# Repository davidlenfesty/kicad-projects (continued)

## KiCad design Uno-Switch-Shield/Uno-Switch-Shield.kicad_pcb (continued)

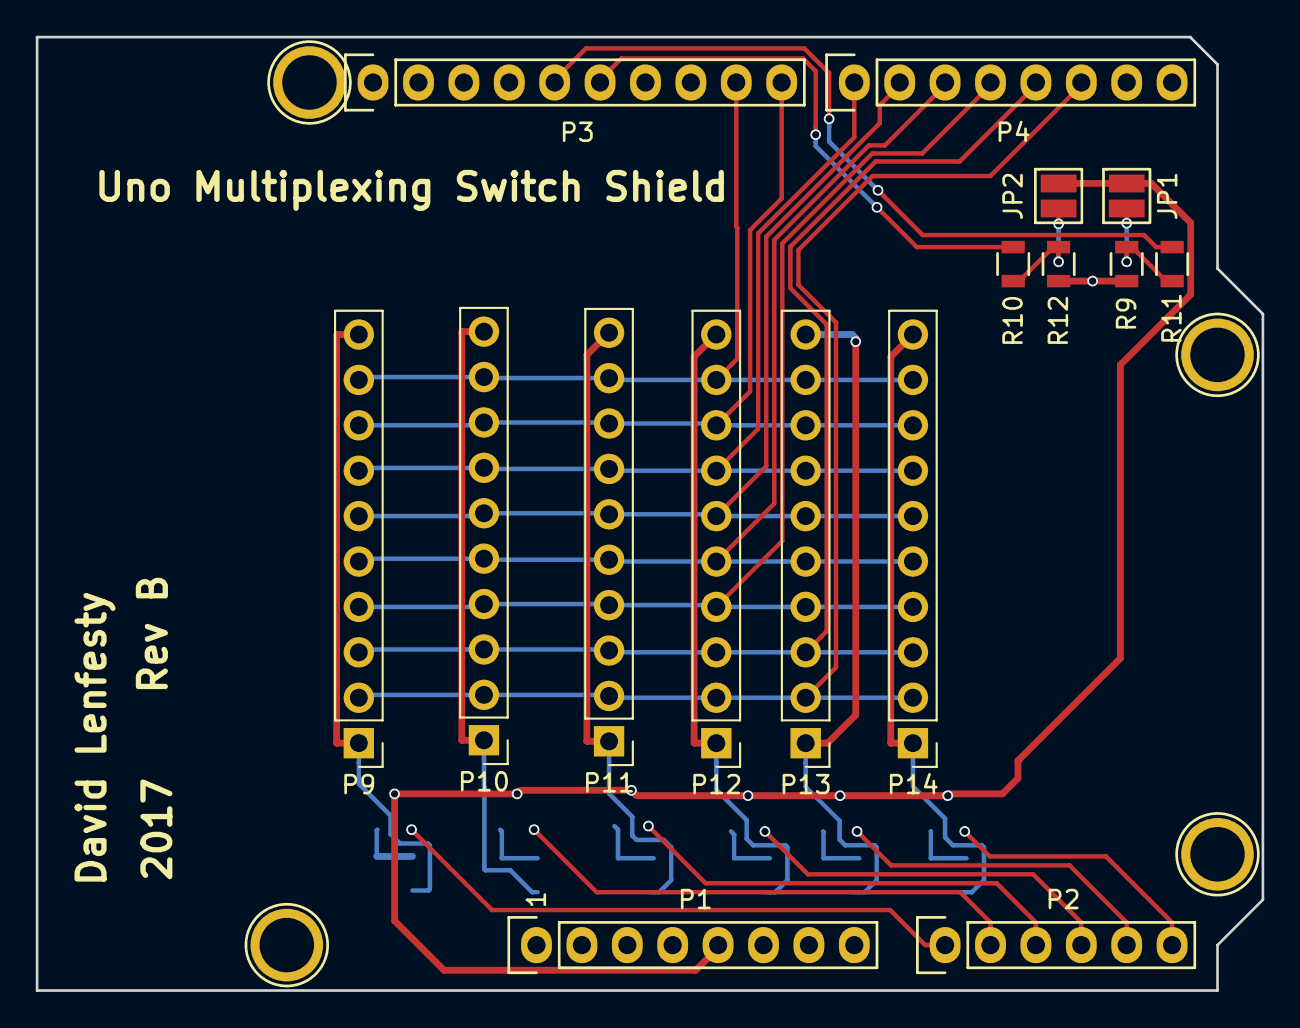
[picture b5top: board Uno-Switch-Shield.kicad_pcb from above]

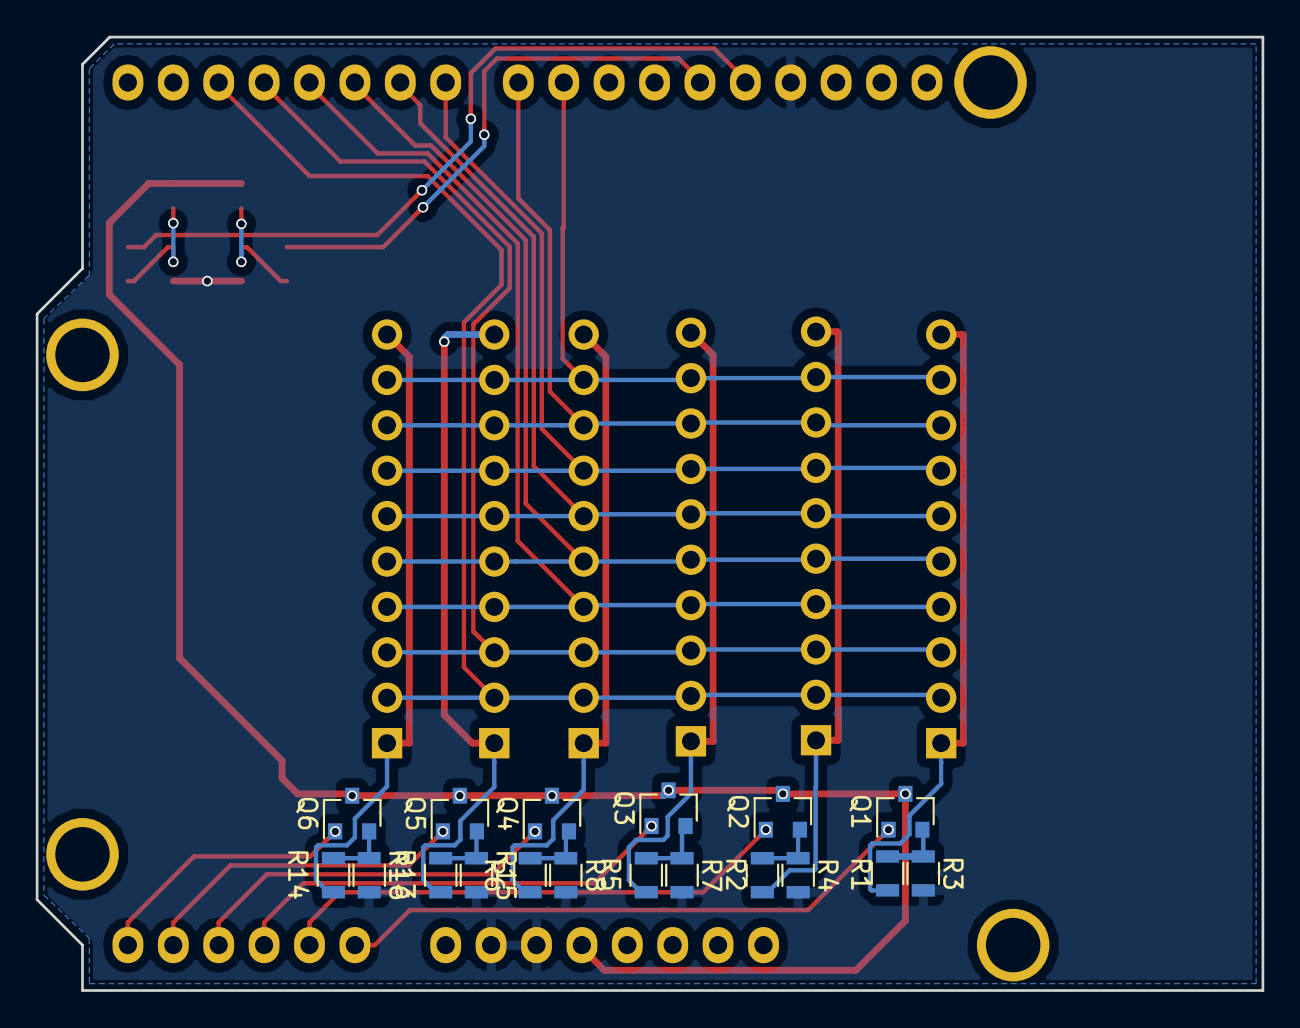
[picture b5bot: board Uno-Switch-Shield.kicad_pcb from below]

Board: 2 copper layers, 68.6 x 53.3 mm, 38 parts (18 on the bottom side), 32 nets.

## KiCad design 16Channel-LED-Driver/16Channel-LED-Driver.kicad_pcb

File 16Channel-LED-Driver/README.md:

# 16 Channel LED Driver Board #

## Intro ##

This is a 16 Channel LED Driver board. Each channel has current limiting (set by the potentiometre/resistor combo by each opamp) and is PWM dimmable. It uses two PCA9634s to do the dimming. Sometime soon I'll come up with a full BOM.

## Decisions ##

I used two PCA9634s and four LM324s just to simplify the routing because initially I figured a two layer board would be simpler to design for personally.

## Revisions ##

### Revision A ###

This was the first revision of the board, had a bunch of issues to fix, a lot of them dumb.

### Revision B ###

The main issue with this revision was lack of resistors in front of the BJTs, so it would pull too much current and overheat the PCA9634s.

### Revision C ###

An issue with the opamp stuff, if you had too high a value for the potentiometre, it would overdrive the BJTs and wreck the opamp.

### Revision D ###

Probably the last revision, unless I decide to completely redo it to make it nicer or put it on a 4 layer board to reduce the size.

## Errata ##

- Consider Rev A and Rev B unusable versions of this board.
- Rev C has an issue where if you turn the potentiometre all the way it will fry the opamp, trying to fix that with Rev D, which as of this commit is not started.

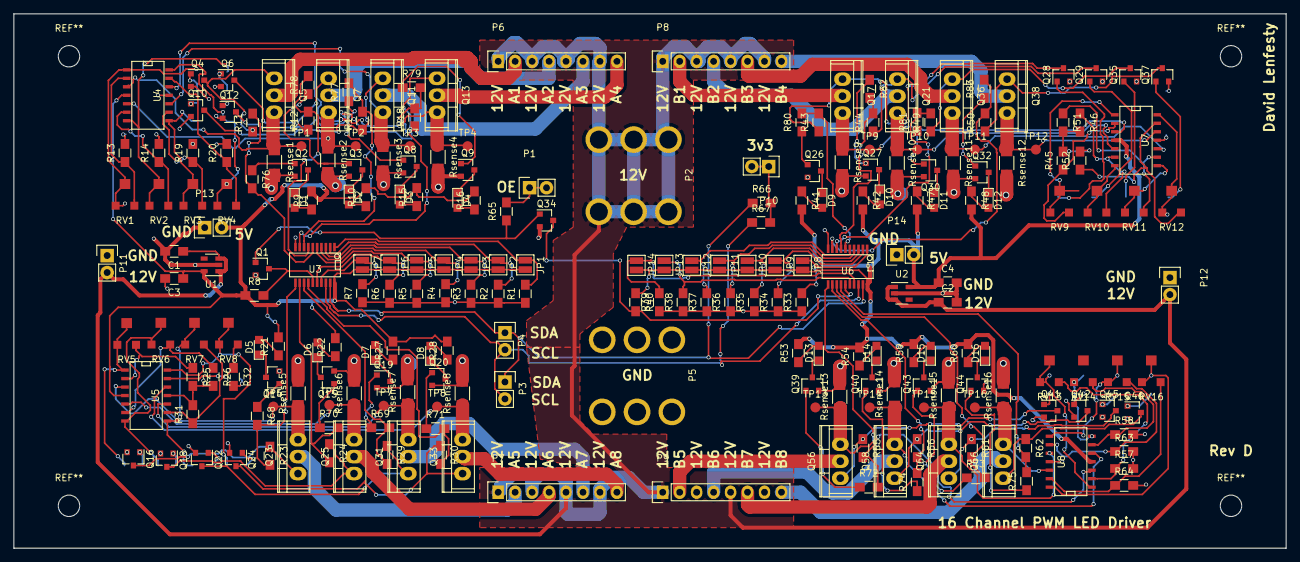
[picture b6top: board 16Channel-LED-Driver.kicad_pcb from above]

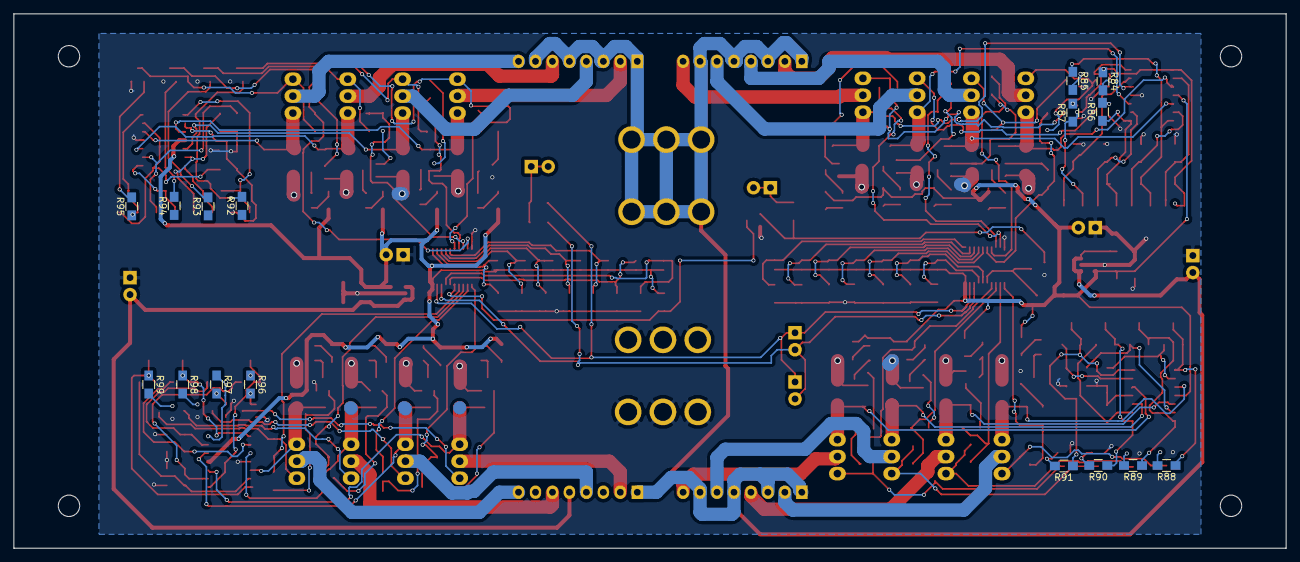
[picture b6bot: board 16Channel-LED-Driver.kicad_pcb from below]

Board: 2 copper layers, 190.5 x 80.0 mm, 253 parts (16 on the bottom side), 185 nets.

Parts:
C1, C2, C3, C4: 1uF; R_0805_HandSoldering
D1, D2, D3, D4, D5, D6, D7, D8, D9, D10, D11, D12, D13, D14, D15, D16: LED; LED_0805
JP1, JP8: A0; Jumper_SMD
JP2, JP9: A1; Jumper_SMD
JP3, JP10: A2; Jumper_SMD
JP4, JP11: A3; Jumper_SMD
JP5, JP12: A4; Jumper_SMD
JP6, JP13: A5; Jumper_SMD
JP7, JP14: A6; Jumper_SMD
P1, P3, P4, P10, P11, P12, P13, P14: CONN_01X02; Socket_Strip_Straight_1x02
P2, P5: CONN_01X06; Screw_Connector_M5
P6, P7, P8, P9: CONN_01X08; Socket_Strip_Straight_1x08
Q1, Q2, Q3, Q4, Q6, Q8, Q9, Q10, Q12, Q14, Q15, Q16, Q18, Q19, Q20, Q22, Q24, Q26, Q27, Q28, Q29, Q30, Q32, Q34, Q35, Q37, Q39, Q40, Q41, Q42, Q43, Q44, Q45, Q46: Q_NPN_BEC; SOT-23
Q5, Q7, Q11, Q13, Q17, Q21, Q23, Q25, Q31, Q33, Q36, Q38, Q56, Q58, Q64, Q66: BUT11; TO-220
R1, R2, R3, R4, R5, R6, R7, R8, R11, R12, R17, R18, R23, R24, R29, R30, R33, R34, R35, R36, R37, R38, R39, R40, R43, R44, R49, R50, R55, R56, R61, R62, R65, R68, R69, R70, R71, R72, R73, R74, R75, R76, R77, R78, R79, R80, R81, R82, R83, R84, R85, R86, R87, R88, R89, R90, R91, R92, R93, R94, R95, R96, R97, R98, R99: 10K; R_0805_HandSoldering
R9, R10, R15, R16, R21, R22, R27, R28, R41, R42, R47, R48, R53, R54, R59, R60: 330; R_0805_HandSoldering
R13, R14, R19, R20, R25, R26, R31, R32, R45, R46, R51, R52, R57, R58, R63, R64: 2K; R_0805_HandSoldering
R66, R67: 4.7K; R_0805_HandSoldering
RV1, RV2, RV3, RV4, RV5, RV6, RV7, RV8, RV9, RV10, RV11, RV12, RV13, RV14, RV15, RV16: 10K; Bourns-TC33
Rsense1, Rsense2, Rsense3, Rsense4, Rsense5, Rsense6, Rsense7, Rsense8, Rsense9, Rsense10, Rsense11, Rsense12, Rsense13, Rsense14, Rsense15, Rsense16: 0.1; R_1206_HandSoldering
TP1, TP2, TP3, TP4, TP5, TP6, TP7, TP8, TP9, TP10, TP11, TP12, TP13, TP14, TP15, TP16: TEST; Measurement_Point_Round-SMD-Pad_Small
U1, U2: LD3985G; SOT-23-5
U3, U6: PCA9634; SSOP-20
U4, U5, U7, U8: LM324AN; SOIC-14_N

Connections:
+3V3: P10.1, P10.2, R66.2, R67.2
+5V-A: C3.1, JP1.2, JP2.2, JP3.2, JP4.2, JP5.2, JP6.2, JP7.2, P13.2, R8.1, R9.2, R10.2, R15.2, R16.2, R21.2, R22.2, R27.2, R28.2, U1.5, U3.20, U4.4, U5.4
+5V-B: C4.1, JP8.2, JP9.2, JP10.2, JP11.2, JP12.2, JP13.2, JP14.2, P14.2, R40.1, R41.2, R42.2, R47.2, R48.2, R53.2, R54.2, R59.2, R60.2, U2.5, U6.20, U7.4, U8.4
+12V: C1.1, C2.1, P2.1, P2.2, P2.3, P2.4, P2.5, P2.6, P6.1, P6.3, P6.5, P6.7, P7.1, P7.3, P7.5, P7.7, P8.1, P8.3, P8.5, P8.7, P9.1, P9.3, P9.5, P9.7, P11.2, P12.2, U1.1, U1.3, U2.1, U2.3
/Power Driver A/LED Driver A/LED1: R11.2, R76.2, U3.6
/Power Driver A/LED Driver A/LED2: R12.2, R78.2, U3.7
/Power Driver A/LED Driver A/LED3: R17.2, R77.2, U3.8
/Power Driver A/LED Driver A/LED4: R18.2, R79.2, U3.9
/Power Driver A/LED Driver B/LED1: R23.2, R68.2, U3.11
/Power Driver A/LED Driver B/LED2: R24.2, R70.2, U3.12
/Power Driver A/LED Driver B/LED3: R29.2, R69.2, U3.13
/Power Driver A/LED Driver B/LED4: R30.2, R71.2, U3.14
/Power Driver B/LED Driver A/LED1: R43.2, R80.2, U6.6
/Power Driver B/LED Driver A/LED2: R44.2, R82.2, U6.7
/Power Driver B/LED Driver A/LED3: R49.2, R81.2, U6.8
/Power Driver B/LED Driver A/LED4: R50.2, R83.2, U6.9
/Power Driver B/LED Driver B/LED1: R55.2, R72.2, U6.11
/Power Driver B/LED Driver B/LED2: R56.2, R74.2, U6.12
/Power Driver B/LED Driver B/LED3: R61.2, R73.2, U6.13
/Power Driver B/LED Driver B/LED4: R62.2, R75.2, U6.14
GND: C1.2, C2.2, C3.2, C4.2, P5.1, P5.2, P5.3, P5.4, P5.5, P5.6, P11.1, P12.1, P13.1, P14.1, Q1.2, Q2.2, Q3.2, Q4.2, Q6.2, Q8.2, Q9.2, Q10.2, Q12.2, Q14.2, Q15.2, Q16.2, Q18.2, Q19.2, Q20.2, Q22.2, Q24.2, Q26.2, Q27.2, Q28.2, Q29.2, Q30.2, Q32.2, Q34.2, Q35.2, Q37.2, Q39.2, Q40.2, Q41.2, Q42.2, Q43.2, Q44.2, Q45.2, Q46.2, R1.1, R2.1, R3.1, R4.1, R5.1, R6.1, R7.1, R13.2, R14.2, R19.2, R20.2, R25.2, R26.2, R31.2, R32.2, R33.1, R34.1, R35.1, R36.1, R37.1, R38.1, R39.1, R45.2, R46.2, R51.2, R52.2, R57.2, R58.2, R63.2, R64.2, Rsense1.2, Rsense2.2, Rsense3.2, Rsense4.2, Rsense5.2, Rsense6.2, Rsense7.2, Rsense8.2, Rsense9.2, Rsense10.2, Rsense11.2, Rsense12.2, Rsense13.2, Rsense14.2, Rsense15.2, Rsense16.2, U1.2, U2.2, U3.10, U4.11, U5.11, U6.10, U7.11, U8.11
unnamed: D1.1, Q2.3
unnamed: D1.2, R9.1
unnamed: D2.1, Q3.3
unnamed: D2.2, R10.1
unnamed: D3.1, Q8.3
unnamed: D3.2, R15.1
unnamed: D4.1, Q9.3
unnamed: D4.2, R16.1
unnamed: D5.1, Q14.3
unnamed: D5.2, R21.1
unnamed: D6.1, Q15.3
unnamed: D6.2, R22.1
unnamed: D7.1, Q19.3
unnamed: D7.2, R27.1
unnamed: D8.1, Q20.3
unnamed: D8.2, R28.1
unnamed: D9.1, Q26.3
unnamed: D9.2, R41.1
unnamed: D10.1, Q27.3
unnamed: D10.2, R42.1
unnamed: D11.1, Q30.3
unnamed: D11.2, R47.1
unnamed: D12.1, Q32.3
unnamed: D12.2, R48.1
unnamed: D13.1, Q39.3
unnamed: D13.2, R53.1
unnamed: D14.1, Q40.3
unnamed: D14.2, R54.1
unnamed: D15.1, Q43.3
unnamed: D15.2, R59.1
unnamed: D16.1, Q44.3
unnamed: D16.2, R60.1
unnamed: JP1.1, R1.2, U3.1
unnamed: JP2.1, R2.2, U3.2
unnamed: JP3.1, R3.2, U3.3
unnamed: JP4.1, R4.2, U3.4
unnamed: JP5.1, R5.2, U3.5
unnamed: JP6.1, R6.2, U3.16
unnamed: JP7.1, R7.2, U3.17
unnamed: JP8.1, R33.2, U6.1
unnamed: JP9.1, R34.2, U6.2
unnamed: JP10.1, R35.2, U6.3
unnamed: JP11.1, R36.2, U6.4
unnamed: JP12.1, R37.2, U6.5
unnamed: JP13.1, R38.2, U6.16
unnamed: JP14.1, R39.2, U6.17
unnamed: P1.1, P1.2, R65.2
unnamed: P6.2, Q5.2
unnamed: P6.4, Q7.2
unnamed: P6.6, Q11.2
unnamed: P6.8, Q13.2
unnamed: P7.2, Q23.2
unnamed: P7.4, Q25.2
unnamed: P7.6, Q31.2
unnamed: P7.8, Q33.2
unnamed: P8.2, Q17.2
unnamed: P8.4, Q21.2
unnamed: P8.6, Q36.2
unnamed: P8.8, Q38.2
unnamed: P9.2, Q56.2
unnamed: P9.4, Q58.2
unnamed: P9.6, Q64.2
unnamed: P9.8, Q66.2
unnamed: Q1.3, R8.2, U3.15
unnamed: Q2.1, R76.1
unnamed: Q3.1, R78.1
unnamed: Q4.1, R84.2
unnamed: Q4.3, Q5.1, R11.1
unnamed: Q5.3, Rsense1.1, TP1.1, U4.3
unnamed: Q6.1, R85.2
unnamed: Q6.3, Q7.1, R12.1
unnamed: Q7.3, Rsense2.1, TP2.1, U4.5
unnamed: Q8.1, R77.1
unnamed: Q9.1, R79.1
unnamed: Q10.1, R86.2
unnamed: Q10.3, Q11.1, R17.1
unnamed: Q11.3, Rsense3.1, TP3.1, U4.10
unnamed: Q12.1, R87.2
unnamed: Q12.3, Q13.1, R18.1
unnamed: Q13.3, Rsense4.1, TP4.1, U4.12
unnamed: Q14.1, R68.1
unnamed: Q15.1, R70.1
unnamed: Q16.1, R88.2
unnamed: Q16.3, Q23.1, R23.1
unnamed: Q17.1, Q28.3, R43.1
unnamed: Q17.3, Rsense9.1, TP9.1, U7.3
unnamed: Q18.1, R89.2
unnamed: Q18.3, Q25.1, R24.1
unnamed: Q19.1, R69.1
unnamed: Q20.1, R71.1
unnamed: Q21.1, Q29.3, R44.1
unnamed: Q21.3, Rsense10.1, TP10.1, U7.5
unnamed: Q22.1, R90.2
unnamed: Q22.3, Q31.1, R29.1
unnamed: Q23.3, Rsense5.1, TP5.1, U5.3
unnamed: Q24.1, R91.2
unnamed: Q24.3, Q33.1, R30.1
unnamed: Q25.3, Rsense6.1, TP6.1, U5.5
unnamed: Q26.1, R80.1
unnamed: Q27.1, R82.1
unnamed: Q28.1, R92.2
unnamed: Q29.1, R93.2
unnamed: Q30.1, R81.1
unnamed: Q31.3, Rsense7.1, TP7.1, U5.10
unnamed: Q32.1, R83.1
unnamed: Q33.3, Rsense8.1, TP8.1, U5.12
unnamed: Q34.3, R40.2, U6.15
unnamed: Q35.1, R94.2
unnamed: Q35.3, Q36.1, R49.1
unnamed: Q36.3, Rsense11.1, TP11.1, U7.10
unnamed: Q37.1, R95.2
unnamed: Q37.3, Q38.1, R50.1
unnamed: Q38.3, Rsense12.1, TP12.1, U7.12
unnamed: Q39.1, R72.1
unnamed: Q40.1, R74.1
unnamed: Q41.1, R96.2
unnamed: Q41.3, Q56.1, R55.1
unnamed: Q42.1, R97.2
unnamed: Q42.3, Q58.1, R56.1
unnamed: Q43.1, R73.1
unnamed: Q44.1, R75.1
unnamed: Q45.1, R98.2
unnamed: Q45.3, Q64.1, R61.1
unnamed: Q46.1, R99.2
unnamed: Q46.3, Q66.1, R62.1
unnamed: Q56.3, Rsense13.1, TP13.1, U8.3
unnamed: Q58.3, Rsense14.1, TP14.1, U8.5
unnamed: Q64.3, Rsense15.1, TP15.1, U8.10
unnamed: Q66.3, Rsense16.1, TP16.1, U8.12
unnamed: R13.1, RV1.3, U4.2
unnamed: R14.1, RV2.3, U4.6
unnamed: R19.1, RV3.3, U4.9
unnamed: R20.1, RV4.3, U4.13
unnamed: R25.1, RV5.3, U5.2
unnamed: R26.1, RV6.3, U5.6
unnamed: R31.1, RV7.3, U5.9
unnamed: R32.1, RV8.3, U5.13
unnamed: R45.1, RV9.3, U7.2
unnamed: R46.1, RV10.3, U7.6
unnamed: R51.1, RV11.3, U7.9
unnamed: R52.1, RV12.3, U7.13
unnamed: R57.1, RV13.3, U8.2
unnamed: R58.1, RV14.3, U8.6
unnamed: R63.1, RV15.3, U8.9
unnamed: R64.1, RV16.3, U8.13
unnamed: R84.1, RV1.1, RV1.2, U4.1
unnamed: R85.1, RV2.1, RV2.2, U4.7
unnamed: R86.1, RV3.1, RV3.2, U4.8
unnamed: R87.1, RV4.1, RV4.2, U4.14
unnamed: R88.1, RV5.1, RV5.2, U5.1
unnamed: R89.1, RV6.1, RV6.2, U5.7
unnamed: R90.1, RV7.1, RV7.2, U5.8
unnamed: R91.1, RV8.1, RV8.2, U5.14
unnamed: R92.1, RV9.1, RV9.2, U7.1
unnamed: R93.1, RV10.1, RV10.2, U7.7
unnamed: R94.1, RV11.1, RV11.2, U7.8
unnamed: R95.1, RV12.1, RV12.2, U7.14
unnamed: R96.1, RV13.1, RV13.2, U8.1
unnamed: R97.1, RV14.1, RV14.2, U8.7
unnamed: R98.1, RV15.1, RV15.2, U8.8
unnamed: R99.1, RV16.1, RV16.2, U8.14
OE-Disable: Q1.1, Q34.1, R65.1
SCL: P3.2, P4.2, R67.1, U3.18, U6.18
SDA: P3.1, P4.1, R66.1, U3.19, U6.19

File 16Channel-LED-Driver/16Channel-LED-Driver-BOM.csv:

Id;Designator;Package;Quantity;Designation;Supplier and ref;;2017-06-09;Notes
1;REF**,REF**,REF**,REF**;MountingHole_3.2mm_M3;4;MountingHole_3.2mm_M3;;;;Don’t Care
2;REF**,REF**,REF**,REF**,REF**,REF**,REF**,REF**,REF**,REF**,REF**,REF**,REF**,REF**,REF**,REF**,REF**,REF**,REF**,REF**,REF**,REF**,REF**,REF**,REF**,REF**,REF**,REF**,REF**,REF**,REF**,REF**,REF**,REF**,REF**,REF**,REF**,REF**,REF**;VIA-0.6mm;39;VIA-0.6mm;;;;Don’t Care
3;Q6,Q4,Q10,Q12,Q8,Q2,Q9,Q3,Q1,Q14,Q15,Q16,Q18,Q19,Q20,Q22,Q24,Q26,Q27,Q28,Q29,Q30,Q32,Q34,Q35,Q37,Q51,Q52,Q55,Q57,Q59,Q60,Q63,Q65;SOT-23;34;BC413;;;Ordered 100;
4;Q7,Q11,Q5,Q13,Q17,Q21,Q23,Q25,Q31,Q33,Q36,Q38,Q56,Q58,Q64,Q66;TO-220;16;BUT11;;;Ordered 16;
5;Rsense2,Rsense4,Rsense3,Rsense1,Rsense5,Rsense6,Rsense7,Rsense8,Rsense9,Rsense10,Rsense11,Rsense12,Rsense13,Rsense14,Rsense15,Rsense16;Current_Sense_Resistor;16;0.1;;;;Not ordering many, not entirely sure about current limiting as of yet
6;RV1,RV3,RV4,RV2,RV5,RV6,RV7,RV8,RV9,RV10,RV11,RV12,RV13,RV14,RV15,RV16;Bourns-TC33;16;10K;;;Ordered 16;
7;R20,R13,R14,R19,R25,R26,R31,R32,R45,R46,R51,R52,R57,R58,R63,R64;R_0805_HandSoldering;16;2K;;;Ordered 20;
8;U4,U5,U7,U8;SOIC-14_N;4;LM324AN;;;Ordered 4;
9;R15,R9,R16,R10,R21,R22,R27,R28,R41,R42,R47,R48,R53,R54,R59,R60;R_0805_HandSoldering;16;330;;;Ordered 20;
10;D3,D1,D4,D2,D5,D6,D7,D8,D9,D10,D11,D12,D13,D14,D15,D16;LED_0805;16;LED;;;Ordered 25;Included in order of other board
11;JP1,JP8;Jumper_SMD;2;A0;;;;Don’t Care
12;JP2,JP9;Jumper_SMD;2;A1;;;;Don’t Care
13;JP3,JP10;Jumper_SMD;2;A2;;;;Don’t Care
14;JP4,JP11;Jumper_SMD;2;A3;;;;Don’t Care
15;JP5,JP12;Jumper_SMD;2;A4;;;;Don’t Care
16;JP6,JP13;Jumper_SMD;2;A5;;;;Don’t Care
17;JP7,JP14;Jumper_SMD;2;A6;;;;Don’t Care
18;P1,P3,P4,P10,P11,P12,P13,P14;Socket_Strip_Straight_1x02;8;CONN_01X02;;;;In other order
19;P2,P5;Screw_Connector_M5;2;CONN_01X06;;;Ordered 2;
20;P6,P7,P8,P9;Socket_Strip_Straight_1x08;4;CONN_01X08;;;Ordered 4;
21;R1,R2,R3,R4,R5,R6,R7,R8,R11,R12,R17,R18,R23,R24,R29,R30,R33,R34,R35,R36,R37,R38,R39,R40,R43,R44,R49,R50,R55,R56,R61,R62,R65;R_0805_HandSoldering;33;10K;;;Ordered 100;
22;R66,R67;R_0805_HandSoldering;2;4.7K;;;Ordered 10;
23;U1,U2;SOT-23-5;2;LD3985G;;;Ordered 2;
24;U3,U6;SSOP-20;2;PCA9634;;;Ordered 2;
25;TP1,TP2,TP3,TP4,TP5,TP6,TP7,TP8,TP9,TP10,TP11,TP12,TP13,TP14,TP15,TP16;Measurement_Point_Round-SMD-Pad_Small;16;TEST;;;;don’t care
26;C1,C2,C3,C4;R_0805_HandSoldering;4;1uF;;;2 1uF and 2 10uF;

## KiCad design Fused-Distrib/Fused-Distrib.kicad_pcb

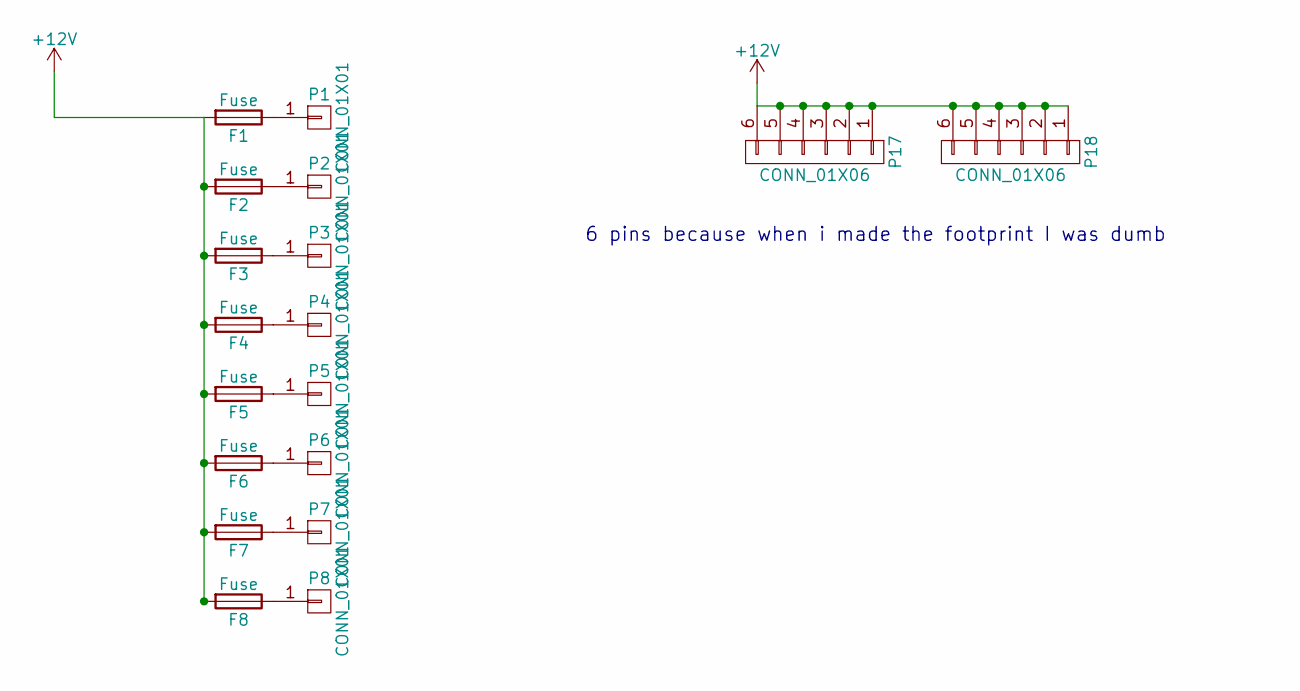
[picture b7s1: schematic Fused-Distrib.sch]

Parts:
F1, F2, F3, F4, F5, F6, F7, F8: Fuse; Fuseholder5x20_horiz_open_lateral_Type-II
P1, P2, P3, P4, P5, P6, P7, P8: CONN_01X01; MountingHole_3.2mm_M3_Pad_Via
P17, P18: CONN_01X06; Screw_Connector_M5

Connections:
+12V: F1.2, F2.2, F3.2, F4.2, F5.2, F6.2, F7.2, F8.2, P17.1, P17.2, P17.3, P17.4, P17.5, P17.6, P18.1, P18.2, P18.3, P18.4, P18.5, P18.6
unnamed: F1.1, P1.1
unnamed: F2.1, P2.1
unnamed: F3.1, P3.1
unnamed: F4.1, P4.1
unnamed: F5.1, P5.1
unnamed: F6.1, P6.1
unnamed: F7.1, P7.1
unnamed: F8.1, P8.1

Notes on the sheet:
6 pins because when i made the footprint I was dumb

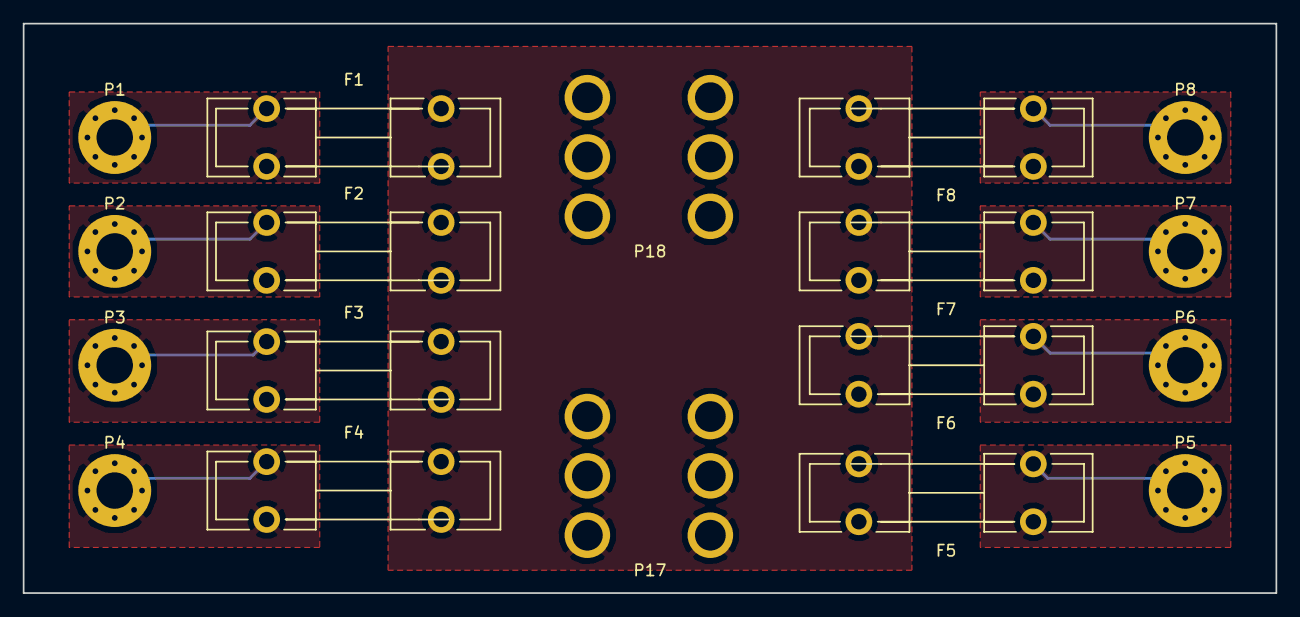
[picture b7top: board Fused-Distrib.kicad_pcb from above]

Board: 2 copper layers, 110.0 x 50.0 mm, 18 parts (0 on the bottom side), 9 nets.

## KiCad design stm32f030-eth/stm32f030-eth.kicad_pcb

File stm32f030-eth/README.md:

# STM32F0-Eth #

This is a small board that uses an STM32F030 and a WIZNet W5500 for ethernet.

Honestly I don't know if this works because when I tested it I ordered the wrong regulator. I ended up not using it and I haven't gotten around to seeing if it works.

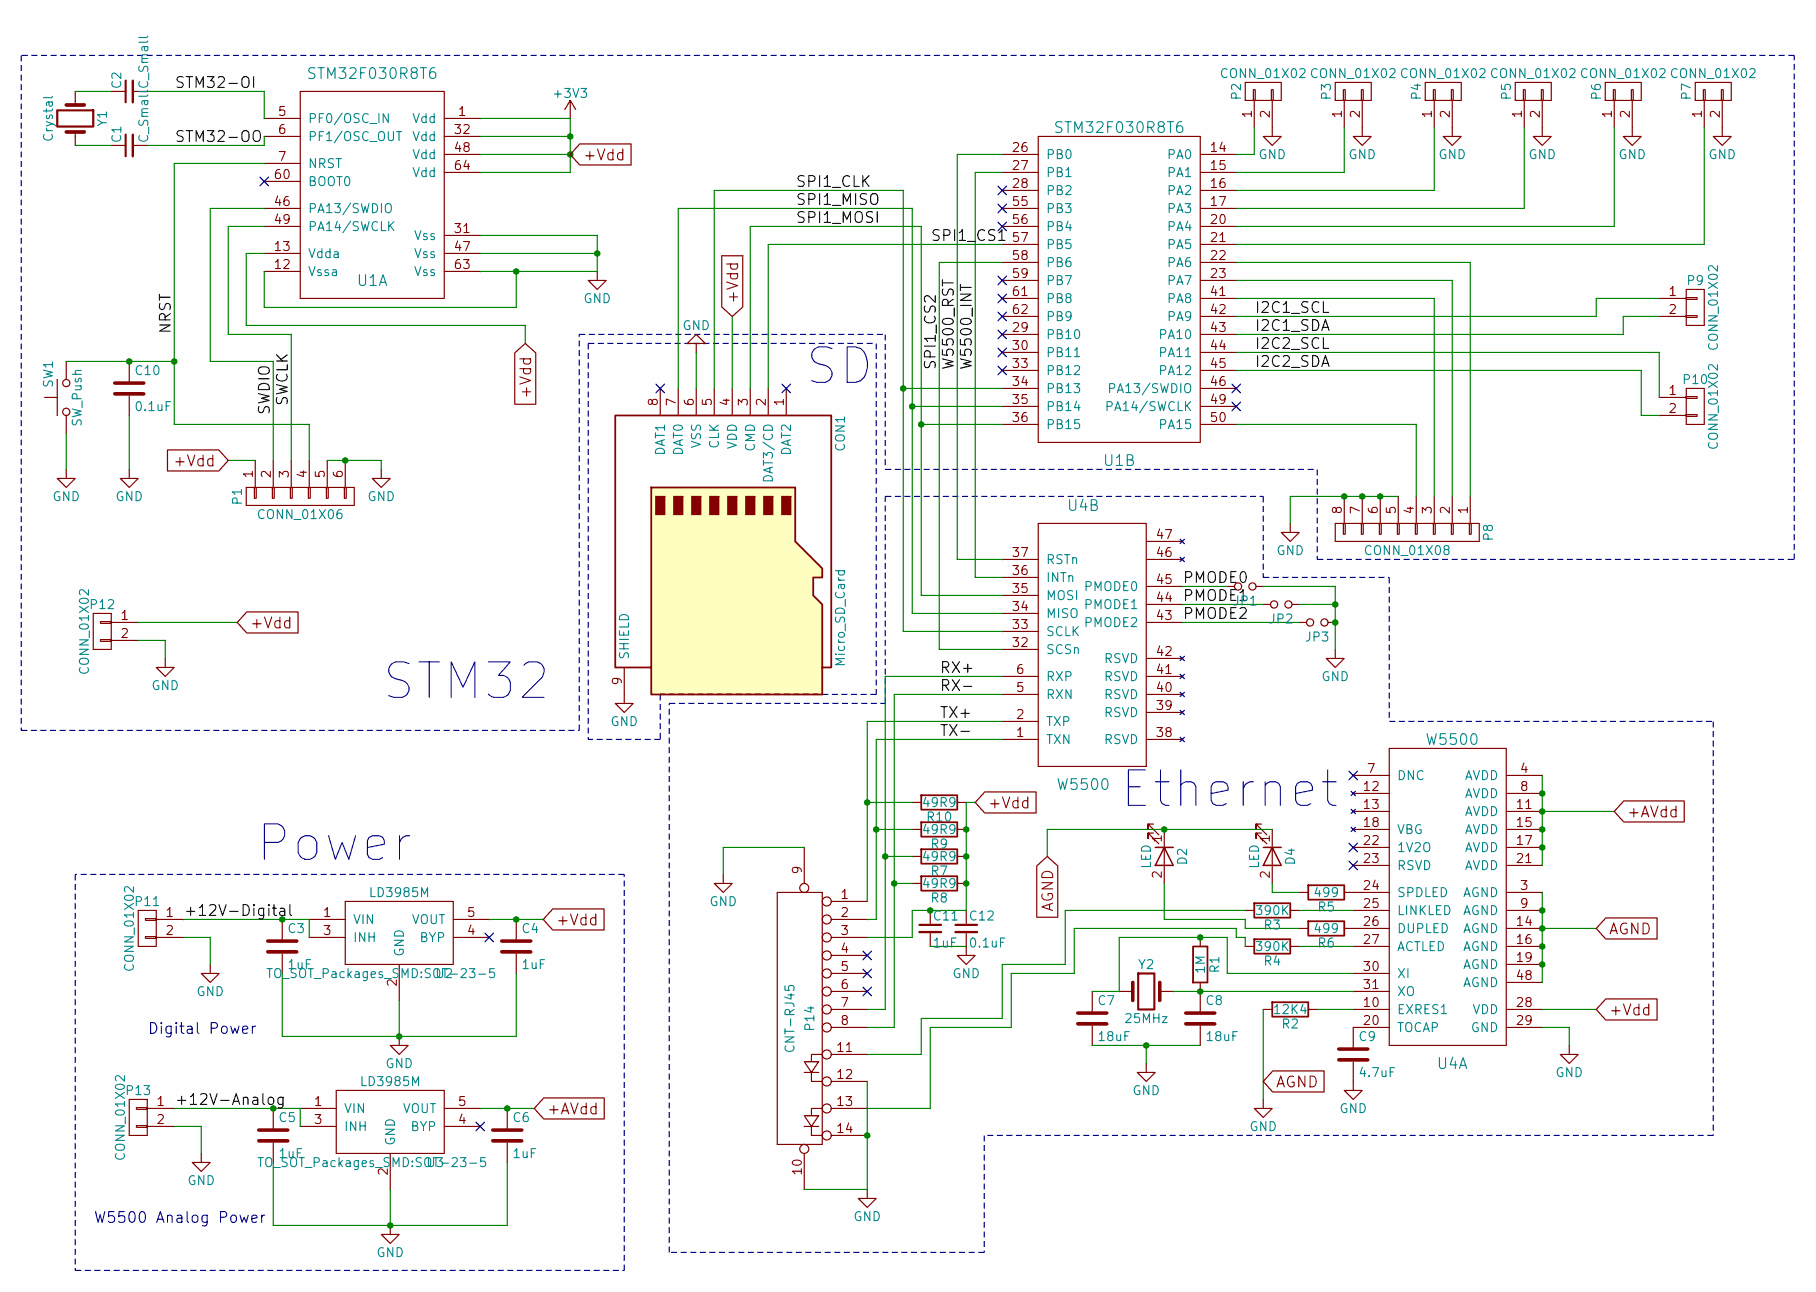
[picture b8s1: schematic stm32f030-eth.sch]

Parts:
C1, C2: C_Small; C_0805_HandSoldering
C3, C4, C5, C6, C11: 1uF; C_0805_HandSoldering
C7, C8: 18uF; C_0805_HandSoldering
C9: 4.7uF; C_0805_HandSoldering
C10, C12: 0.1uF; C_0805_HandSoldering
CON1: Micro_SD_Card; microSD-5031821852
D2, D4: LED; LED_0805
JP1, JP2, JP3: Jumper_NO_Small; Jumper_SMD
P1: CONN_01X06; Socket_Strip_Straight_1x06
P2, P3, P4, P5, P6, P7, P9, P10, P11, P12, P13: CONN_01X02; Socket_Strip_Straight_1x02
P8: CONN_01X08; Socket_Strip_Straight_1x08
P14: CNT-RJ45; 8p8c-RB1-125BAG1A
R1: 1M; R_0805_HandSoldering
R2: 12K4; R_0805_HandSoldering
R3, R4: 390K; R_0805_HandSoldering
R5, R6: 499; R_0805_HandSoldering
R7, R8, R9, R10: 49R9; R_0805_HandSoldering
SW1: SW_Push; SW_SPST_B3S-1000
U1: STM32F030R8T6; LQFP-64_10x10mm_Pitch0.5mm
U2, U3: LD3985M; SOT-23-5
U4: W5500; LQFP-48_7x7mm_Pitch0.5mm
Y1: Crystal; Crystal_SMD_HC49-SD_HandSoldering
Y2: 25MHz; Crystal_SMD_HC49-SD_HandSoldering

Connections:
+AVdd: C6.1, U3.5 (VOUT), U4.4 (AVDD), U4.8 (AVDD), U4.11 (AVDD), U4.15 (AVDD), U4.17 (AVDD), U4.21 (AVDD)
+Vdd: C4.1, C11.1, C12.1, CON1.4 (VDD), P1.1, P12.1, P14.3, R7.1, R8.1, R9.1, R10.1, U1.1 (Vdd), U1.13 (Vdda), U1.32 (Vdd), U1.48 (Vdd), U1.64 (Vdd), U2.5 (VOUT), U4.28 (VDD)
/+12V-Analog: C5.1, P13.1, U3.1 (VIN), U3.3 (INH)
/+12V-Digital: C3.1, P11.1, U2.1 (VIN), U2.3 (INH)
/I2C1_SCL: P9.1, U1.42 (PA9)
/I2C1_SDA: P9.2, U1.43 (PA10)
/I2C2_SCL: P10.1, U1.44 (PA11)
/I2C2_SDA: P10.2, U1.45 (PA12)
/NRST: C10.1, P1.4, SW1.2, U1.7 (NRST)
/PMODE0: JP1.2, U4.45 (PMODE0)
/PMODE1: JP2.2, U4.44 (PMODE1)
/PMODE2: JP3.2, U4.43 (PMODE2)
/RX+: P14.7, R7.2, U4.6 (RXP)
/RX-: P14.8, R8.2, U4.5 (RXN)
/SPI1_CLK: CON1.5 (CLK), U1.34 (PB13), U4.33 (SCLK)
/SPI1_CS1: CON1.2 (DAT3/CD), U1.57 (PB5)
/SPI1_CS2: U1.58 (PB6), U4.32 (SCSn)
/SPI1_MISO: CON1.7 (DAT0), U1.35 (PB14), U4.34 (MISO)
/SPI1_MOSI: CON1.3 (CMD), U1.36 (PB15), U4.35 (MOSI)
/STM32-OI: C2.2, U1.5 (PF0/OSC_IN)
/STM32-OO: C1.2, U1.6 (PF1/OSC_OUT)
/SWCLK: P1.3, U1.49 (PA14/SWCLK)
/SWDIO: P1.2, U1.46 (PA13/SWDIO)
/TX+: P14.1, R10.2, U4.2 (TXP)
/TX-: P14.2, R9.2, U4.1 (TXN)
/W5500_INT: U1.27 (PB1), U4.36 (INTn)
/W5500_RST: U1.26 (PB0), U4.37 (RSTn)
AGND: C3.2, C4.2, C5.2, C6.2, C7.2, C8.2, C9.2, C10.2, C11.2, C12.2, CON1.6 (VSS), CON1.9 (SHIELD), D2.1 (K), D4.1 (K), JP1.1, JP2.1, JP3.1, P1.5, P1.6, P2.2, P3.2, P4.2, P5.2, P6.2, P7.2, P8.5, P8.6, P8.7, P8.8, P11.2, P12.2, P13.2, P14.9, P14.10, P14.12, P14.14, R2.2, SW1.1, U1.12 (Vssa), U1.31 (Vss), U1.47 (Vss), U1.63 (Vss), U2.2 (GND), U3.2 (GND), U4.3 (AGND), U4.9 (AGND), U4.14 (AGND), U4.16 (AGND), U4.19 (AGND), U4.29 (GND), U4.48 (AGND)
unnamed: C1.1, Y1.2
unnamed: C2.1, Y1.1
unnamed: C7.1, R1.1, U4.30 (XI), Y2.1
unnamed: C8.1, R1.2, U4.31 (XO), Y2.2
unnamed: C9.1, U4.20 (TOCAP)
unnamed: D2.2 (A), R6.2
unnamed: D4.2 (A), R5.2
unnamed: P2.1, U1.14 (PA0)
unnamed: P3.1, U1.15 (PA1)
unnamed: P4.1, U1.16 (PA2)
unnamed: P5.1, U1.17 (PA3)
unnamed: P6.1, U1.20 (PA4)
unnamed: P7.1, U1.21 (PA5)
unnamed: P8.1, U1.22 (PA6)
unnamed: P8.2, U1.23 (PA7)
unnamed: P8.3, U1.41 (PA8)
unnamed: P8.4, U1.50 (PA15)
unnamed: P14.11, R3.2
unnamed: P14.13, R4.2
unnamed: R2.1, U4.10 (EXRES1)
unnamed: R3.1, U4.25 (LINKLED)
unnamed: R4.1, U4.27 (ACTLED)
unnamed: R5.1, U4.24 (SPDLED)
unnamed: R6.1, U4.26 (DUPLED)

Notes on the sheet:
W5500 Analog Power
Digital Power
Power
STM32
Ethernet

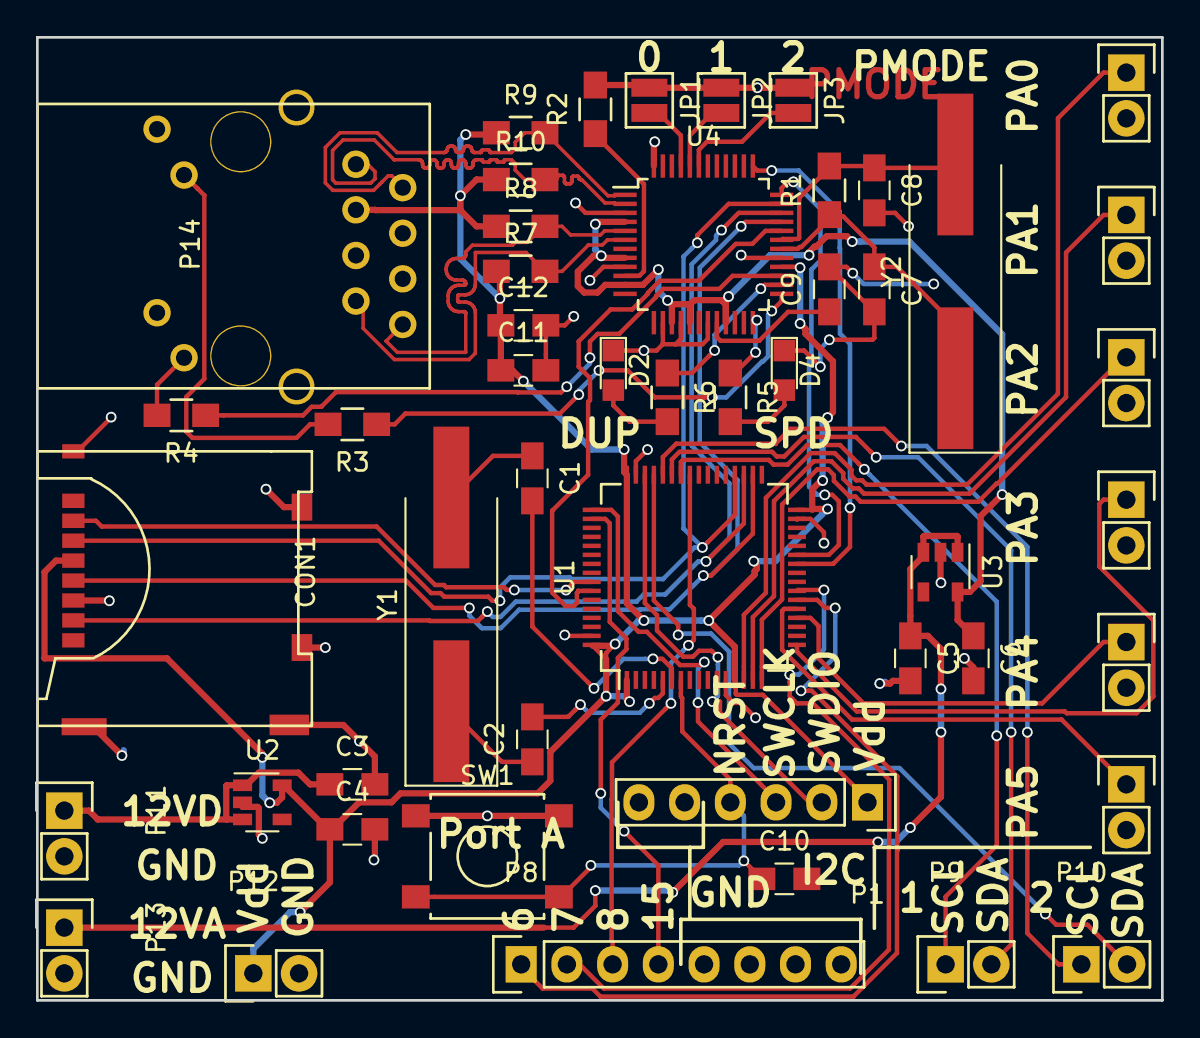
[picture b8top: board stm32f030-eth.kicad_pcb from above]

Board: 2 copper layers, 62.5 x 53.5 mm, 49 parts (0 on the bottom side), 52 nets.

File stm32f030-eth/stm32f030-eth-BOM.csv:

Id		Package	Quantity	Designation	Supplier and ref	Designator		2017-03-07	Notes
1		LQFP-48_7x7mm_Pitch0.5mm	1	W5500		U4			
2		C_0805_HandSoldering	2	C_Small		C1,C2			Not ordering
3		C_0805_HandSoldering	5	1uF		C3,C4,C5,C6,C11			
4		C_0805_HandSoldering	2	18uF		C7,C8			PICOFARADS Change this in schematic
5		C_0805_HandSoldering	1	0.1uF		C12			
6		microSD-5031821852	1	Micro_SD_Card		CON1			
7		LED_0805	2	LED		D2,D4			Same partno for this board and for the driver board
8		Jumper_SMD	3	Jumper_NO_Small		JP1,JP2,JP3			
9		Socket_Strip_Straight_1x06	1	CONN_01X06		P1			
10		Socket_Strip_Straight_1x02	11	CONN_01X02		P2,P3,P4,P5,P6,P7,P9,P10,P11,P12,P13			
11		Socket_Strip_Straight_1x08	1	CONN_01X08		P8			
12		8p8c-RB1-125BAG1A	1	CNT-RJ45		P14			
13		R_0805_HandSoldering	1	1M		R1			
14		R_0805_HandSoldering	1	12K4		R2			
15		R_0805_HandSoldering	2	390K		R3,R4			
16		R_0805_HandSoldering	2	499		R5,R6			
17		R_0805_HandSoldering	4	49R9		R7,R8,R9,R10			
18		LQFP-64_10x10mm_Pitch0.5mm	1	STM32F030R8T6		U1			
19		SOT-23-5	2	LD3985M		U2,U3			
20		Crystal_SMD_HC49-SD_HandSoldering	1	Crystal		Y1			
21		Crystal_SMD_HC49-SD_HandSoldering	1	25MHz		Y2			
22		C_0805_HandSoldering	1	4.7uF		C9

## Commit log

2015-11-13 Added Lime-GPIO expander
2015-11-13 Just cleaning some file stuff up, added .gitignore
2015-11-13 dammit
2015-11-13 Finished cleaning stuff up, fixed .gitignore
2015-11-13 created gerbers + zip for uploading to oshpark
2015-11-13 Started new small project for a 3channel pwm driver
2017-01-06 I guess I should actually start comitting this stuff, huh. Maybe so it's not only on my computer. This adds most of my work on the 3 channel board. and all the work on the 16-channel one. and maybe s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
2017-02-07 Finished most of the work on the 16 Channel LED driver, finished RevA at least. There are still a few vestigal folders to delete and stuff to clean, but I'm lazy.
2017-02-07 Changed README
2017-02-12 Designed the first revision of a simple stm32 board
2017-02-12 fixed a dumb mistake on the stm32f030-basic board
2017-02-16 Finished first revision of stm32f030-eth
2017-02-16 forgot a few silkscreen words
2017-03-24 Fixed some errors in the 8p8c connector. Added a reset switch. Added a BOM
2017-07-24 Added another project, mostly saving up so I can do rev B of the 16 channel board
2017-07-25 Did Revision B of the 16 Channel board, also exported some gerbers
2017-07-27 Added a new switch shield
2017-08-09 Did third and hopefully final revision of the 16 channel LED board. I like making dumb mistakes. :(
2017-08-09 Added a little SOIC soldering practice board
2017-08-14 Added a little fused power distro board.
2017-10-07 Added a README to the 16-channel board Don't use the 16 Channel board until the next commit, it has some serious issues
2017-10-08 Rev D of the 16 Channel board. Fixed an issue with the opamp driving BJTs
2017-10-08 Added some more information to the README for the 16 channel board.
2017-10-08 Some housecleaning of projects I don't care about.
2017-11-24 Finished schematic for Altoids Power Supply Also did a few footprints, most of them not needed.
2017-11-24 Added a README for the Altoids Power Supply
2017-11-28 Rev A possibly complete, need to review to ensure no errors. Generated some preliminary gerbers to check things.
2017-11-28 Finished Revision A. Exported gerbers.
2017-12-03 Made the Uno Switch Shield six headers instead of four. Also some re-exporting of gerbers.
2017-12-05 Updated Altoids PSU Readme
2017-12-05 Re-exported some gerbers
2017-12-05 Started Rev B of Altoids PSU.
2017-12-05 Added a README
2017-12-06 Exported some PNGs; Added a BOM; Modified a README
2018-05-01 Designed a simple AC dimmer circuit. (untested)
2018-07-09 Added AC-LED-Control Project
2018-07-10 Added some stuff for AC LED control.
    Expect more in the future.
2018-07-10 Enabled ignoring of swap files
2018-07-10 Added notes.md and started digital stuff.
    - Added notes.md
    - Added bypass caps to STM32
    - Added I2C stuff
    - Added 2 SN74HC595's and various nets
2018-07-10 More notes
2018-07-11 Pulled BOOT0 to GND
2018-07-11 Added SWD
2018-07-11 Added FOD814-D Component
2018-07-11 Added zero cross detector
2018-07-11 Added LTV-846S component
2018-07-11 Added 16 TRIAC outputs
2018-07-11 more stuff
2018-07-11 Added Lite-on SMD-16 footprint
2018-07-11 Added ONSEMI PDIP4 footprint
2018-07-11 Associated footprints
2018-07-11 Added indication LEDs, 3v3 current specs and some initial layout
2018-07-11 Created VXO7803-1000 3v3 power regulator
2018-07-11 Added 3v3 power regulator
2018-07-11 Associated LEDs
2018-07-24 Modified some values for finding components
2018-07-24 Saved state on july 23
2018-07-24 Changed up isolation scheme and added BOM
    Instead of isolating each of the TRIAC channels individually,
    I changed it so the system uses an isolated power supply and isolates
    itself from I2C as well.
    Basic BOM was started as well.
2018-07-25 Added DPAK and SIP-4 packages
2018-07-25 Finished final associations and tweaks
2018-07-25 Changed TRIAC from DPAK part to T0-202-3 part.
2018-07-25 Lots of layout + added a diode.
    I realised that the power regulator might need protection from the 3v3
    line on the programming header.
    Added a diode just in case.
2018-07-25 Finished most placement and ac control lines.
    Finished up general placement of components.
    Also did most of the control lines for the AC side of things.
2018-07-25 Should mostly be done.
    Needs to be checked over.
2018-07-25 Tweaked power planes
2018-07-25 Removed diode and fixed some dumb DRC errors.
    I had to add some vias where they really weren't needed but whatever.
2018-07-25 Removed diode from BOM.
2018-08-20 Some random stuff like gerbers
2019-01-12 Added README to AC-LED-Control
2019-11-17 Finished relay shift register thingy
2019-12-04 Added gerbers for relay shift board
